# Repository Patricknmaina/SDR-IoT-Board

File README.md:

# SDR‑IoT‑Board

An IoT-based edge device and ground-station platform designed for telemetry and mission data—integrated with a 1U nanosatellite workflow. The hardware centers on an ESP32‑S3 module with LoRa, microSD storage, battery management/charging, sensor interfaces, and multiple expansion headers for rapid prototyping and deployment.

<p align="center">
  
  <br/>
  
  <br/>
  
  <br/>
</p>

## Table of Contents

- Overview
- Key Features
- Hardware Architecture
- Power Architecture
- Interfaces and Connectors
- Major Components
- Project Structure
- Manufacturing (Gerbers, BOM, CPL)
- Bring‑Up Checklist
- Firmware Getting Started
- Mechanical and 3D Models
- License
- Acknowledgements and Notes

## Overview

This repository contains the complete KiCad design for the IoT Edge Device v1.0, including schematic, PCB layout, fabrication outputs, custom footprints, and mechanical models. No firmware is included in this repository; the board is intended to be programmed using the ESP32‑S3’s native USB interface (ESP‑IDF or Arduino‑ESP32).

Use cases include ground-station telemetry collection, environmental sensing, edge data logging, and LoRa-based long-range links to remote nodes or satellite payload testbeds.

## Key Features

- ESP32‑S3‑WROOM‑1‑N16R8 module (16 MB flash, 8 MB PSRAM)
- LoRa radio module (Ai‑Thinker RA‑02, SPI interface)
- microSD storage (SPI mode selected; design notes on SPI vs. SDIO)
- Environmental sensing: BME280 (I2C; default address 0x76), DHT11 header
- Multiple I2C expansion headers for quick peripheral add‑ons
- Two UART headers for serial peripherals and diagnostics
- Relay driver header (external 5 V relay module), driven via ESP32‑S3 GPIO6 through 1 kΩ
- Native USB (Micro‑B) with ESD protection for data and power
- Battery management/boost via IP5306 module; status LEDs for charge/level
- 3.3 V rail via AMS1117‑3.3 LDO
- 32.768 kHz RTC crystal for ESP32‑S3 (ESR ≤ 70 kΩ per note)

## Hardware Architecture

- Microcontroller: ESP32‑S3‑WROOM‑1‑N16R8 (`IoT Edge Device v1.0/IoT Edge Device V1.kicad_sch`)
- Radio: RA‑02 LoRa (SPI: `MOSI_LORA`, `MISO_LORA`, `SCLK_LORA`, `CS_LORA`)
- Storage: microSD (SPI: `MOSI_SD`, `MISO_SD`, `SCLK_SD`, `CS_SD`)
- Sensors: BME280 on I2C (SDO pulled Low → default 0x76), DHT11 via single‑wire `DHT_DATA` header
- Expansion: three I2C headers (`SCL_OUT`, `SDA_OUT`), SPI header, UART1/2 headers
- Control: Relay header driven from ESP32‑S3 GPIO6 via 1 kΩ current‑limit resistor
- Clocking: 32.768 kHz crystal for RTC; ensure ESR ≤ 70 kΩ
- Protection: SP05xxx ESD array on USB; Schottky diodes for power ORing

Notes
- Design text documents the choice of SPI over SDIO for simplicity (SDIO is faster but higher complexity/CPU tradeoffs).
- Exact ESP32 GPIO mappings for the above nets are defined in the schematic; see the KiCad file for authoritative pinout and update firmware pin definitions accordingly.

## Power Architecture

- Sources: 5 V via USB Micro‑B and from IP5306 boost output; diode‑OR prevents back‑feeding.
- Solar input: 12 V panel → external LM7805 module → 5 V for IP5306 input (see design note). For higher efficiency and thermal margin, a buck regulator is recommended over linear.
- Battery: IP5306 manages charging and provides 5 V output; LED indicators for charge and capacity.
- 3.3 V rail: AMS1117‑3.3 LDO powers ESP32‑S3, LoRa, and sensors.

Recommendations
- Consider replacing the 12 V→5 V LM7805 path with a high‑efficiency buck (e.g., LM2596/MP1584) to reduce heat and increase battery/runtime performance.
- Validate 3.3 V load headroom (ESP32‑S3 + LoRa TX + SD activity) and thermal dissipation for the LDO.

## Interfaces and Connectors

- USB: Micro‑B connector; native ESP32‑S3 USB (D+ / D−) for flashing and CDC; ESD protection present.
- I2C: labeled I2C1 / I2C2 / I2C3 headers on `SCL_OUT` and `SDA_OUT` nets.
- SPI: dedicated header labeled “SPI Connector”.
- UART: UART1 and UART2 headers; UART2 noted for DAC use case.
- Relay: external 5 V relay module header; controlled by ESP32‑S3 GPIO6 via 1 kΩ series resistor.
- SD Card: microSD socket (SPI wiring).
- LoRa: RA‑02 module (SPI wiring with dedicated CS).

## Major Components

- X1: ESP32‑S3‑WROOM‑1‑N16R8 (MCU + Wi‑Fi/BLE, native USB)
- U6: Ai‑Thinker RA‑02 LoRa module (SPI)
- J15: microSD socket (Hirose DM3D‑SF)
- U8: BME280 environmental sensor (I2C, default 0x76)
- DHT11: external module via header (`DHT_DATA`)
- U5: IP5306 battery charger/boost controller
- U1: AMS1117‑3.3 linear regulator
- J1: USB Micro‑B connector
- D2: SP05xxx ESD protection for USB
- D4–D7: DFLS130L‑7 Schottky diodes (power ORing)
- Y1: 32.768 kHz crystal for RTC

See `IoT Edge Device v1.0/Fab Files/IoT BOM.csv` for the full sourced BOM (with JLCPCB part numbers) and `IoT Edge Device v1.0/Fab Files/IoT CPL.csv` for centroid/placements.

## Project Structure

- `IoT Edge Device v1.0/` — KiCad project (schematic, PCB, project metadata)
  - `IoT Edge Device V1.kicad_sch` — Schematic
  - `IoT Edge Device V1.kicad_pcb` — PCB layout
  - `Fab Files/` — Gerbers, drill, BOM, CPL for fabrication and assembly
  - `Fabrication Outputs.zip` — Consolidated fab package
- `Design Resources/` — Custom footprints and STEP models
- `Images/` — Renders and module screenshots used in this README

## Manufacturing (Gerbers, BOM, CPL)

All files required for fab and assembly are provided:

1) Gerbers and Drill
- Path: `IoT Edge Device v1.0/Fab Files/*gbr`, `.../IoT Edge Device V1.drl`

2) Bill of Materials
- Path: `IoT Edge Device v1.0/Fab Files/IoT BOM.csv` (includes JLCPCB part numbers)

3) Pick & Place (Centroid)
- Path: `IoT Edge Device v1.0/Fab Files/IoT CPL.csv` (Top placements)

## Firmware Getting Started

- Toolchains: ESP‑IDF (v5.x) or Arduino‑ESP32 with S3 support
- Transport: Native USB (CDC) for flashing and serial output
- Pin definitions: Map nets from the schematic to firmware pins:
  - LoRa SPI: `MOSI_LORA`, `MISO_LORA`, `SCLK_LORA`, `CS_LORA`
  - SD SPI: `MOSI_SD`, `MISO_SD`, `SCLK_SD`, `CS_SD`
  - I2C: `SDA_OUT`, `SCL_OUT`
  - DHT11: `DHT_DATA`
  - Relay: `GPIO6`

Since the ESP32 GPIO numbers tied to these nets can vary by routing, use the KiCad schematic (`.kicad_sch`) as the source of truth and set your firmware `gpio_num_t` values accordingly.

Libraries
- LoRa: `arduino-lmic` or `RadioLib` (Arduino), or ESP‑IDF SPI drivers with Semtech HAL equivalents
- microSD: `SD`/`SdFat` (Arduino) or ESP‑IDF `sdspi_host`
- BME280: Adafruit/ESP‑IDF drivers (I2C)
- DHT11: Adafruit (Arduino) or a simple single‑wire driver

## Mechanical and 3D Models

- STEP models for key parts are under `Design Resources/STEP Files/` (ESP32‑S3 module, RA‑02, IP5306, microSD, crystal, etc.)
- Use these for enclosure fit, heatsinking studies, and cable clearance.

## License

This project is released under the MIT License. See `LICENSE` for details.

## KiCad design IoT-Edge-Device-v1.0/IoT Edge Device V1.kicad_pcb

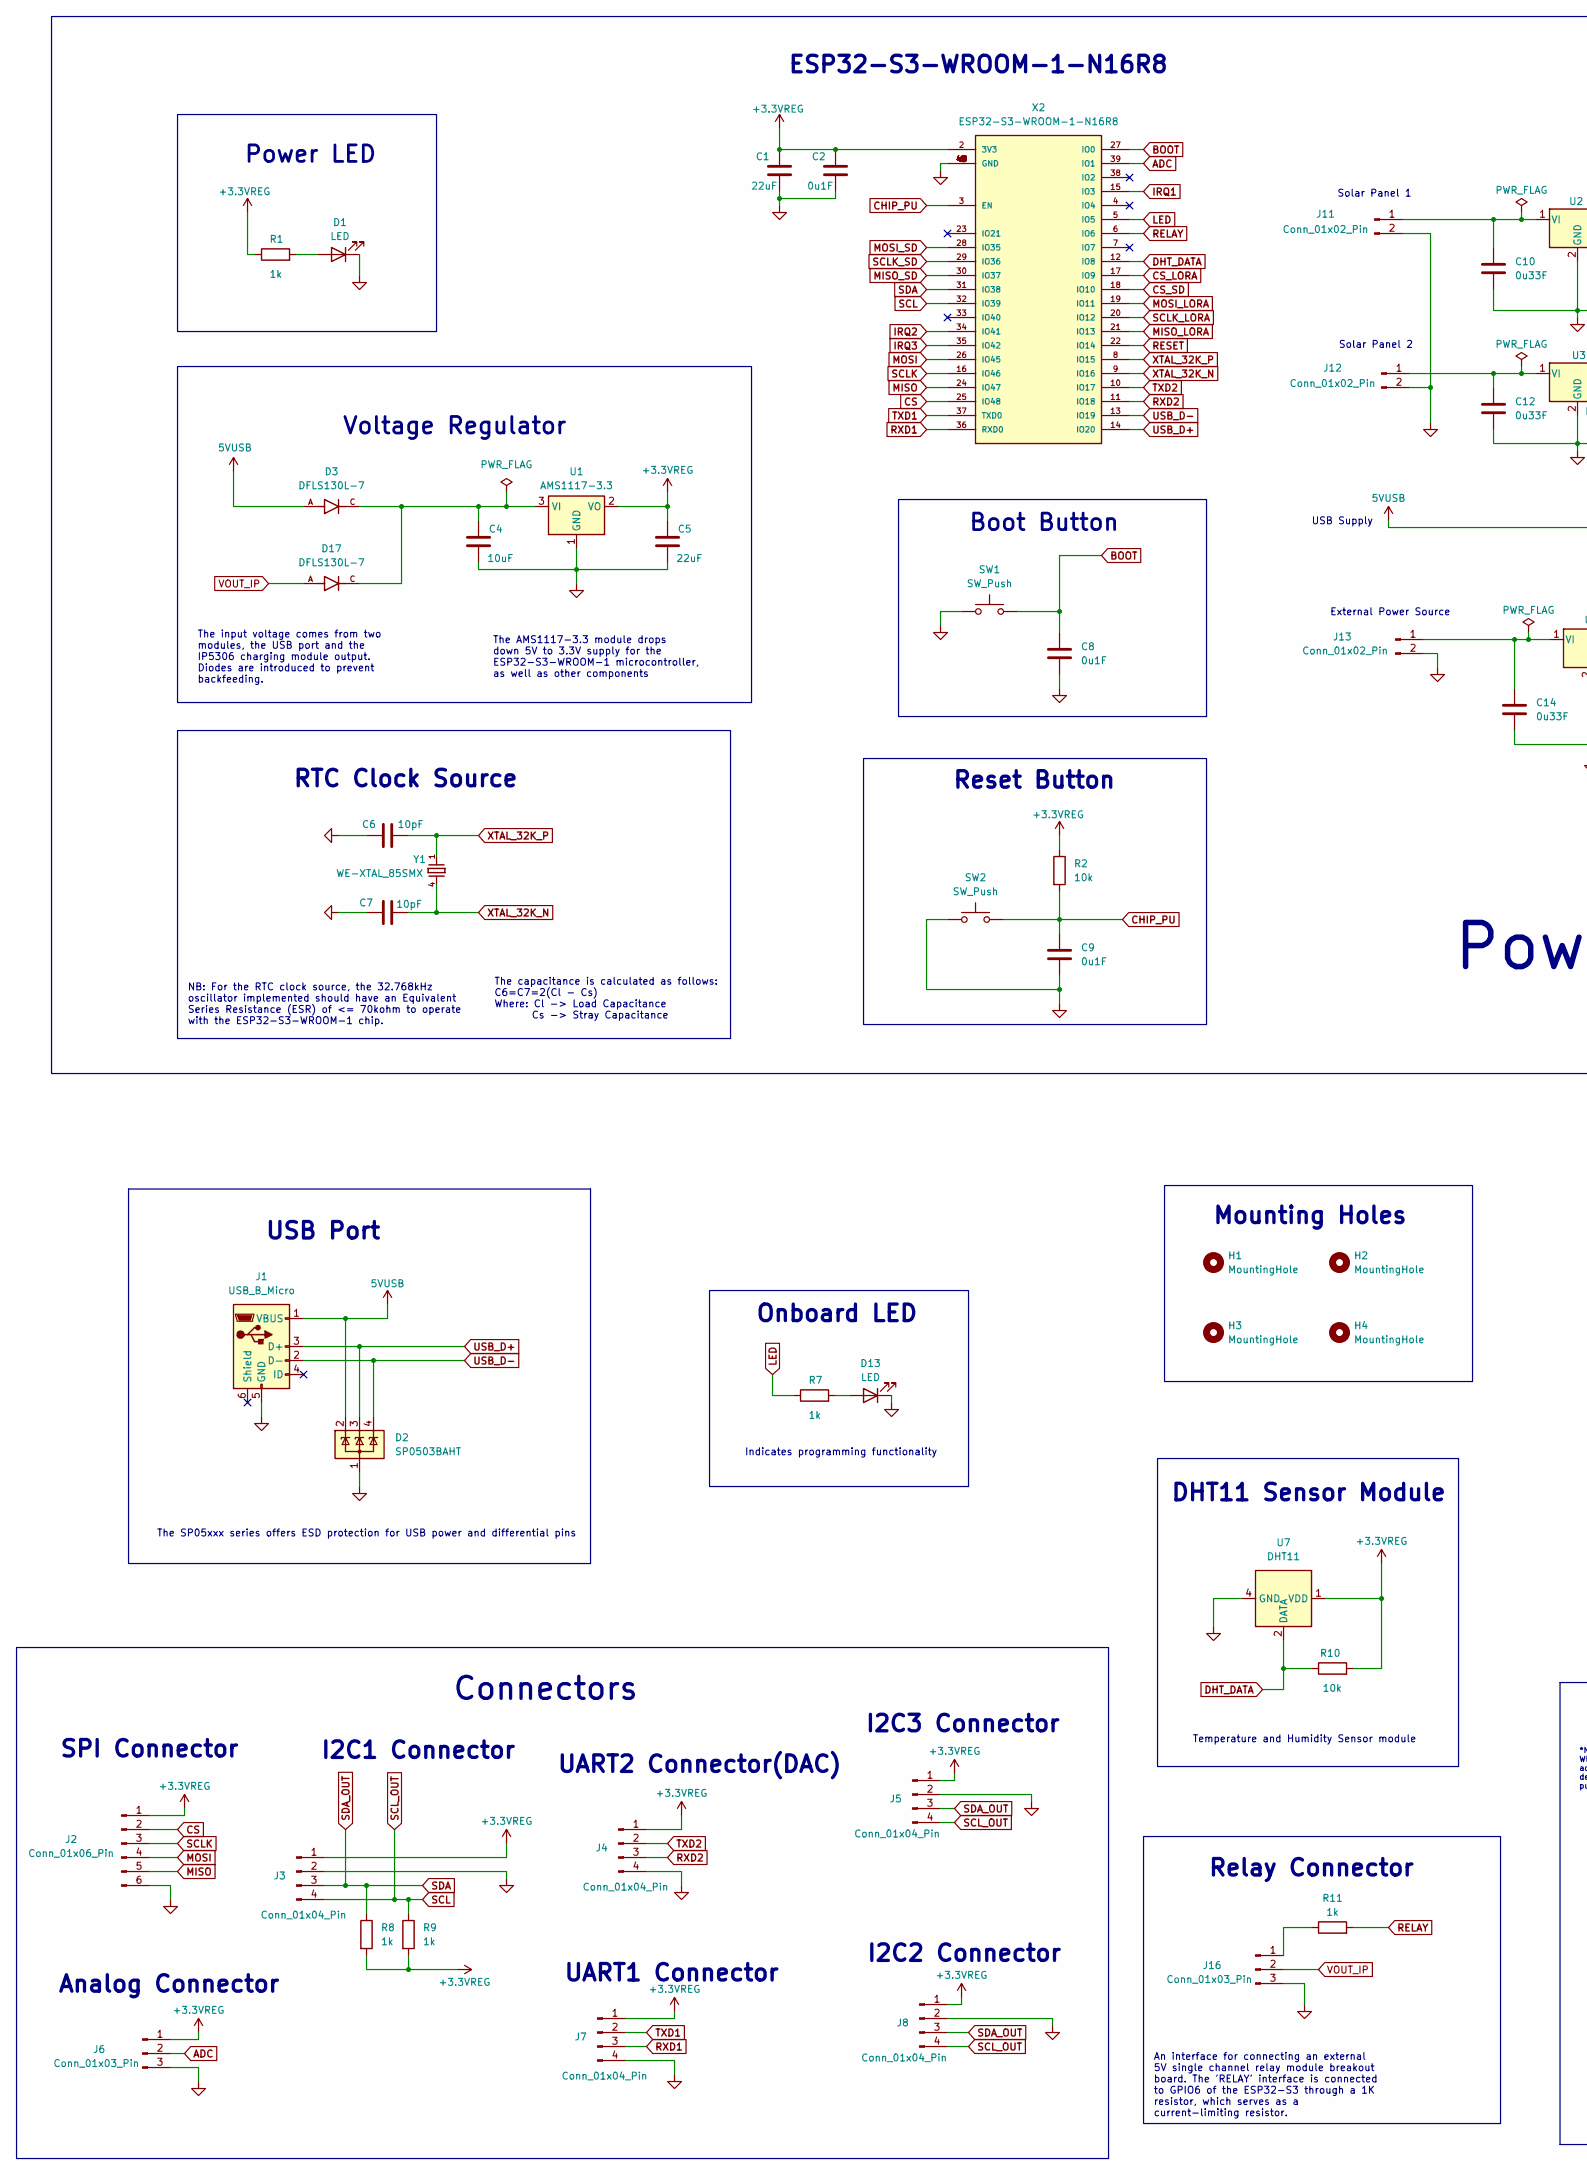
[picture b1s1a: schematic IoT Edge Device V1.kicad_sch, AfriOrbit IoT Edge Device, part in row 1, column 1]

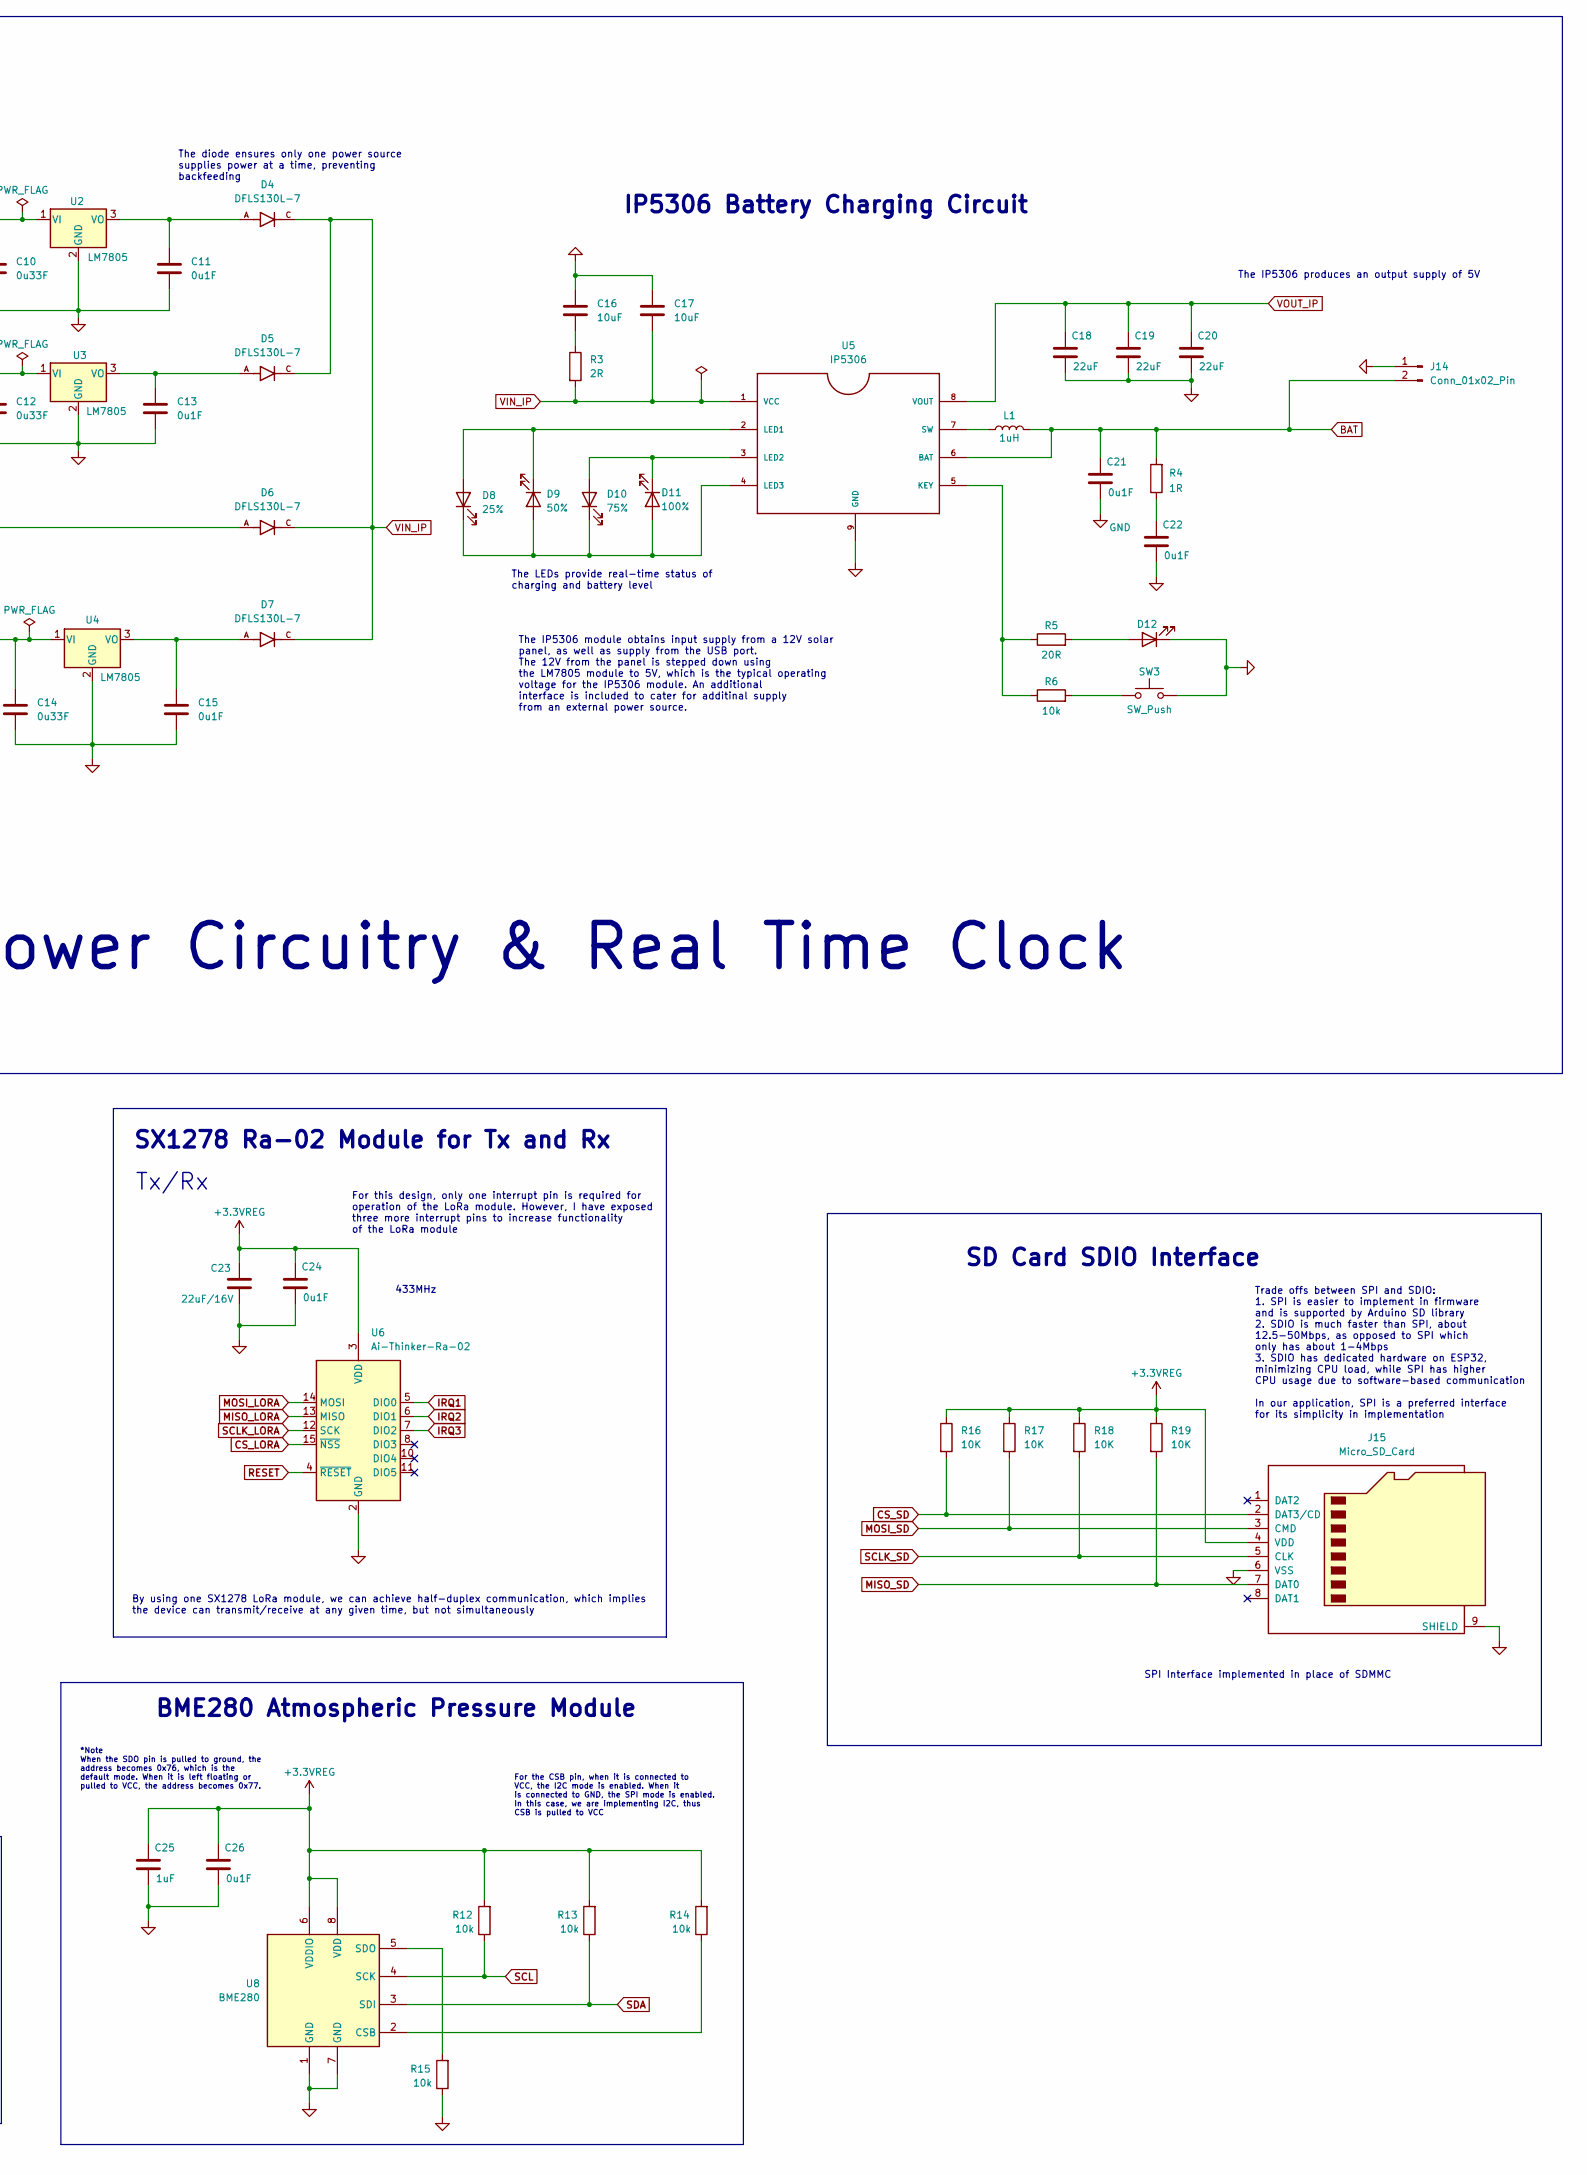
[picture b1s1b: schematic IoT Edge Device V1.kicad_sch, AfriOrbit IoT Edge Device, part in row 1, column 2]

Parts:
C1, C5, C18, C19, C20: 22uF; C_0603_1608Metric
C2, C8, C9, C11, C13, C15, C21, C22, C24, C26: 0u1F; C_0402_1005Metric
C4, C16, C17: 10uF; C_0402_1005Metric
C6, C7: 10pF; C_0402_1005Metric
C10, C12, C14: 0u33F; C_0402_1005Metric
C23: 22uF/16V; C_0603_1608Metric
C25: 1uF; C_0402_1005Metric
D1, D12, D13: LED; LED_0603_1608Metric
D2: SP0503BAHT; SOT-143
D3, D4, D5, D6, D7, D17: DFLS130L-7; DIO_DFLS130L-7; PARTREV 5 - 2
D8: 25%; LED_0603_1608Metric
D9: 50%; LED_0603_1608Metric
D10: 75%; LED_0603_1608Metric
D11: 100%; LED_0603_1608Metric
H1, H2, H3, H4: MountingHole; MountingHole_3.2mm_M3
J1: USB_B_Micro; USB_Micro-B_Wuerth_629105150521
J2: Conn_01x06_Pin; JST_XH_B6B-XH-A_1x06_P2.50mm_Vertical
J3, J4, J5, J7, J8: Conn_01x04_Pin; JST_XH_B4B-XH-A_1x04_P2.50mm_Vertical
J6, J16: Conn_01x03_Pin; JST_XH_B3B-XH-A_1x03_P2.50mm_Vertical
J11, J12, J13: Conn_01x02_Pin; JST_XH_B2B-XH-A_1x02_P2.50mm_Vertical
J14: Conn_01x02_Pin; PinHeader_1x02_P2.54mm_Vertical
J15: Micro_SD_Card; microSD_HC_Hirose_DM3D-SF
L1: 1uH; L_0402_1005Metric
R1, R7, R8, R9, R11: 1k; R_0402_1005Metric
R2, R6, R10, R12, R13, R14, R15: 10k; R_0402_1005Metric
R3: 2R; R_0402_1005Metric
R4: 1R; R_0402_1005Metric
R5: 20R; R_0402_1005Metric
R16, R17, R18, R19: 10K; R_0402_1005Metric
SW1, SW2, SW3: SW_Push; SW_PUSH_6mm
U1: AMS1117-3.3; SOT-223-3_TabPin2
U2, U3, U4: LM7805; TO-220-3_Vertical
U5: IP5306; SOIC9P127_490X600X170L84X42T330X241N
U6: Ai-Thinker-Ra-02; MODULE_RA-02_LORA
U7: DHT11; Aosong_DHT11_5.5x12.0_P2.54mm
U8: BME280; Bosch_LGA-8_2.5x2.5mm_P0.65mm_ClockwisePinNumbering
X2: ESP32-S3-WROOM-1-N16R8; ESP32S3WROOM1N8R2; MANUFACTURER_PART_NUMBER ESP32-S3-WROOM-1-N16R8
Y1: WE-XTAL_85SMX

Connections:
5VUSB: D2.2 (K), D3.A, D6.A, J1.1 (VBUS)
+3.3VREG: C1.1, C2.1, C5.1, C23.1, C24.1, C25.1, C26.1, J2.1, J3.1, J4.1, J5.1, J6.1, J7.1, J8.1, J15.4 (VDD), R1.1, R2.1, R8.2, R9.2, R10.2, R12.2, R13.2, R14.2, R16.1, R17.1, R18.1, R19.1, U1.2 (VO), U6.3 (VDD), U7.1 (VDD), U8.6 (VDDIO), U8.8 (VDD), X2.2 (3V3); also elsewhere on the board
ADC: J6.2, X2.39 (IO1); also elsewhere on the board
BAT: C21.1, J14.2, L1.2, R4.2, U5.6 (BAT)
BOOT: C8.1, SW1.2, X2.27 (IO0); also elsewhere on the board
CHIP_PU: C9.1, R2.2, SW2.2, X2.3 (EN); also elsewhere on the board
CS: J2.2, X2.25 (IO48); also elsewhere on the board
CS_LORA: U6.15 (~NSS), X2.17 (IO9); also elsewhere on the board
CS_SD: J15.2 (DAT3/CD), R16.2, X2.18 (IO10); also elsewhere on the board
DHT_DATA: R10.1, U7.2 (DATA), X2.12 (IO8); also elsewhere on the board
GND: C1.2, C2.2, C4.2, C5.2, C6.1, C7.1, C8.2, C9.2, C10.2, C11.2, C12.2, C13.2, C14.2, C15.2, C16.1, C17.1, C18.2, C19.2, C20.2, C21.2, C22.2, C23.2, C24.2, C25.2, C26.2, D1.1 (K), D2.1 (A), D12.1 (K), D13.1 (K), J1.5 (GND), J2.6, J3.2, J4.4, J5.2, J6.3, J7.4, J8.2, J11.2, J12.2, J13.2, J14.1, J15.6 (VSS), J15.9 (SHIELD), J16.3, R15.1, SW1.1, SW2.1, SW3.2, U1.1 (GND), U2.2 (GND), U3.2 (GND), U4.2 (GND), U5.9 (GND), U6.1 (GND), U6.2 (GND), U6.9 (GND), U6.16 (GND), U7.4 (GND), U8.1 (GND), U8.7 (GND), X2.1 (GND), X2.40 (GND), X2.41 (GND), X2.42 (GND), X2.43 (GND), X2.44 (GND), X2.45 (GND), X2.46 (GND), X2.47 (GND), X2.48 (GND), X2.49 (GND); also elsewhere on the board
IRQ1: U6.5 (DIO0), X2.15 (IO3); also elsewhere on the board
IRQ2: U6.6 (DIO1), X2.34 (IO41); also elsewhere on the board
IRQ3: U6.7 (DIO2), X2.35 (IO42); also elsewhere on the board
LED: R7.1, X2.5 (IO5); also elsewhere on the board
MISO: J2.5, X2.24 (IO47); also elsewhere on the board
MISO_LORA: U6.13 (MISO), X2.21 (IO13); also elsewhere on the board
MISO_SD: J15.7 (DAT0), R19.2, X2.30 (IO37); also elsewhere on the board
MOSI: J2.4, X2.26 (IO45); also elsewhere on the board
MOSI_LORA: U6.14 (MOSI), X2.19 (IO11); also elsewhere on the board
MOSI_SD: J15.3 (CMD), R17.2, X2.28 (IO35); also elsewhere on the board
unnamed: C16.2, R3.1
unnamed: C22.1, R4.1
unnamed: D1.2 (A), R1.2
unnamed: D8.2 (A), D9.1 (K), U5.2 (LED1)
unnamed: D10.2 (A), D11.1 (K), U5.3 (LED2)
unnamed: D8.1 (K), D9.2 (A), D10.1 (K), D11.2 (A), U5.4 (LED3)
unnamed: D12.2 (A), R5.2
unnamed: D13.2 (A), R7.2
unnamed: C10.1, J11.1, U2.1 (VI)
unnamed: C12.1, J12.1, U3.1 (VI)
unnamed: C14.1, J13.1, U4.1 (VI)
unnamed: J16.1, R11.1
unnamed: R6.2, SW3.1
unnamed: C4.1, D3.C, D17.C, U1.3 (VI)
unnamed: C11.1, D4.A, U2.3 (VO)
unnamed: C13.1, D5.A, U3.3 (VO)
unnamed: C15.1, D7.A, U4.3 (VO)
unnamed: R5.1, R6.1, U5.5 (KEY)
unnamed: L1.1, U5.7 (SW)
unnamed: R14.1, U8.2 (CSB)
unnamed: R15.2, U8.5 (SDO)
RELAY: R11.2, X2.6 (IO6); also elsewhere on the board
RESET: U6.4 (~RESET), X2.22 (IO14); also elsewhere on the board
RXD1: J7.3, X2.36 (RXD0); also elsewhere on the board
RXD2: J4.3, X2.11 (IO18); also elsewhere on the board
SCL: J3.4, J5.4, J8.4, R9.1, R12.1, U8.4 (SCK), X2.32 (IO39); also elsewhere on the board
SCLK: J2.3, X2.16 (IO46); also elsewhere on the board
SCLK_LORA: U6.12 (SCK), X2.20 (IO12); also elsewhere on the board
SCLK_SD: J15.5 (CLK), R18.2, X2.29 (IO36); also elsewhere on the board
SDA: J3.3, J5.3, J8.3, R8.1, R13.1, U8.3 (SDI), X2.31 (IO38); also elsewhere on the board
TXD1: J7.2, X2.37 (TXD0); also elsewhere on the board
TXD2: J4.2, X2.10 (IO17); also elsewhere on the board
USB_D+: D2.3 (K), J1.3 (D+), X2.14 (IO20); also elsewhere on the board
USB_D-: D2.4 (K), J1.2 (D-), X2.13 (IO19); also elsewhere on the board
VIN_IP: C17.2, D4.C, D5.C, D6.C, D7.C, R3.2, U5.1 (VCC)
VOUT_IP: C18.1, C19.1, C20.1, D17.A, J16.2, U5.8 (VOUT)
XTAL_32K_N: C7.2, X2.9 (IO16), Y1.4; also elsewhere on the board
XTAL_32K_P: C6.2, X2.8 (IO15), Y1.1; also elsewhere on the board

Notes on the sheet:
SPI Connector
The capacitance is calculated as follows: C6=C7=2(Cl - Cs) Where: Cl -> Load Capacitance Cs -> Stray Capacitance
The input voltage comes from two modules, the USB port and the IP5306 charging module output. Diodes are introduced to prevent backfeeding.
I2C1 Connector
The IP5306 produces an output supply of 5V
*Note When the SDO pin is pulled to ground, the address becomes 0x76, which is the default mode. When it is left floating or pulled to VCC, the address becomes 0x77.
Mounting Holes
USB Port
UART2 Connector(DAC)
Tx/Rx
433MHz
BME280 Atmospheric Pressure Module
SX1278 Ra-02 Module for Tx and Rx
Connectors
Temperature and Humidity Sensor module
By using one SX1278 LoRa module, we can achieve half-duplex communication, which implies the device can transmit/receive at any given time, but not simultaneously
An interface for connecting an external 5V single channel relay module breakout board. The 'RELAY' interface is connected to GPIO6 of the ESP32-S3 through a 1K resistor, which serves as a current-limiting resistor.
Analog Connector
Power Circuitry & Real Time Clock
I2C3 Connector
Relay Connector
NB: For the RTC clock source, the 32.768kHz oscillator implemented should have an Equivalent Series Resistance (ESR) of <= 70kohm to operate with the ESP32-S3-WROOM-1 chip.
RTC Clock Source
I2C2 Connector
For the CSB pin, when it is connected to VCC, the I2C mode is enabled. When it is connected to GND, the SPI mode is enabled. In this case, we are implementing I2C, thus CSB is pulled to VCC
Boot Button
UART1 Connector
SPI Interface implemented in place of SDMMC
The IP5306 module obtains input supply from a 12V solar panel, as well as supply from the USB port. The 12V from the panel is stepped down using the LM7805 module to 5V, which is the typical operating voltage for the IP5306 module. An additional interface is included to cater for additinal supply f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
The LEDs provide real-time status of charging and battery level
Voltage Regulator
Trade offs between SPI and SDIO: 1. SPI is easier to implement in firmware and is supported by Arduino SD library 2. SDIO is much faster than SPI, about 12.5-50Mbps, as opposed to SPI which only has about 1-4Mbps 3. SDIO has dedicated hardware on ESP32, minimizing CPU load, while SPI has higher CPU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
Onboard LED
Reset Button
ESP32-S3-WROOM-1-N16R8
Power LED
Indicates programming functionality
DHT11 Sensor Module
Solar Panel 1
IP5306 Battery Charging Circuit

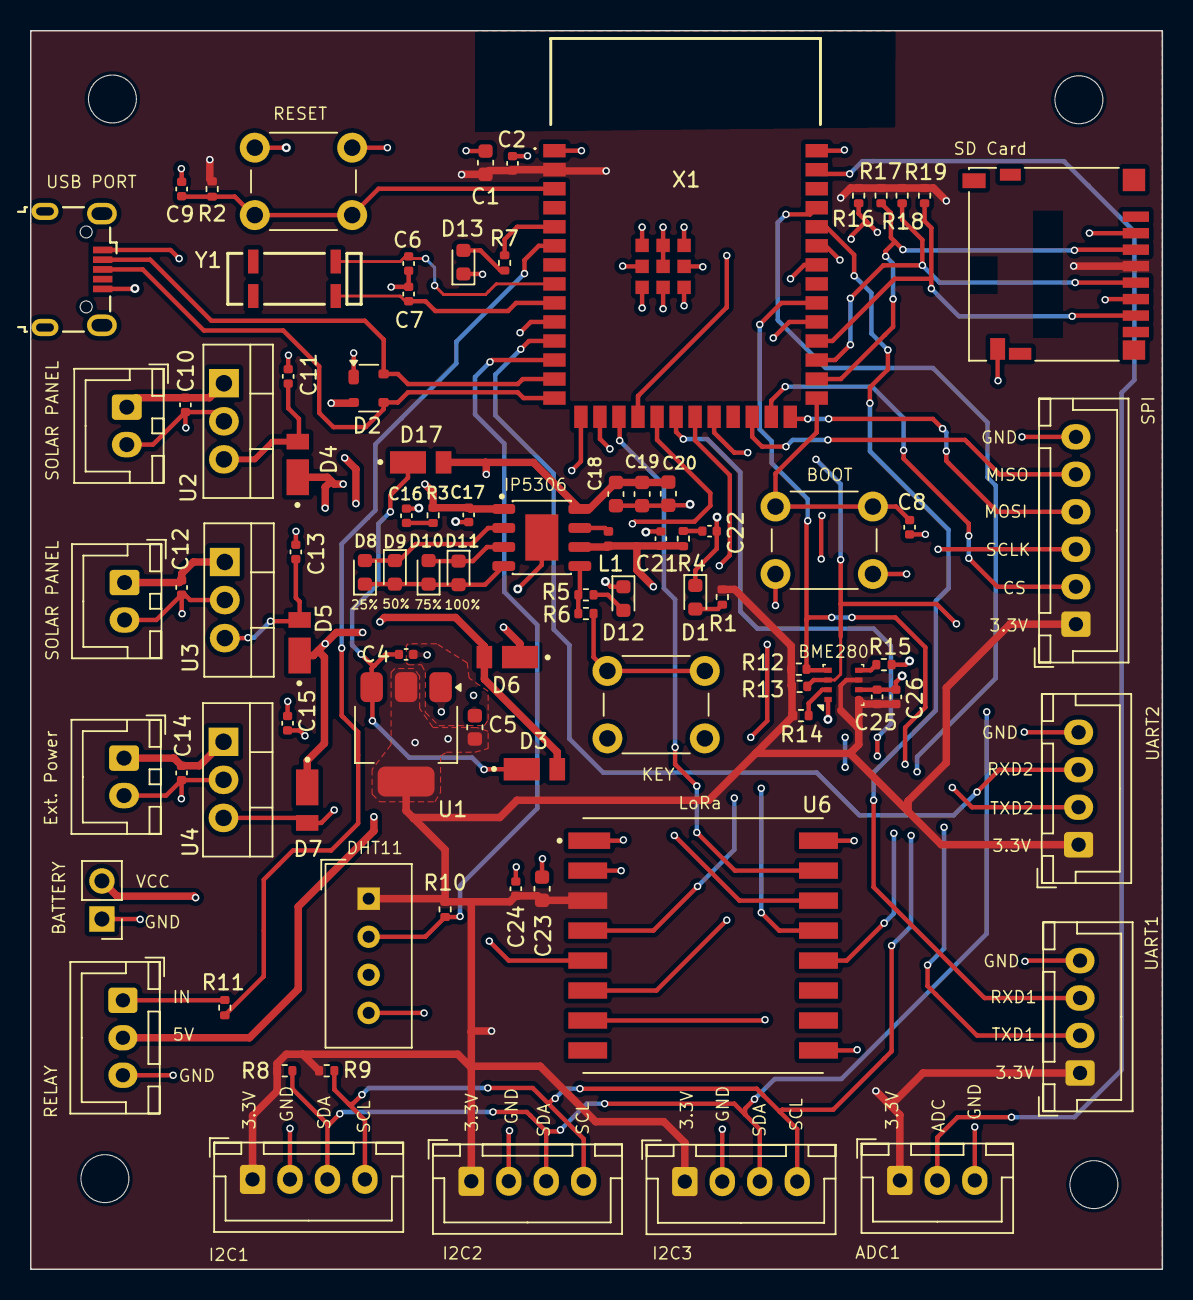
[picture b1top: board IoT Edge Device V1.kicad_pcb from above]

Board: 4 copper layers, 75.5 x 82.7 mm, 90 parts (0 on the bottom side), 59 nets.

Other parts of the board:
X1: ESP32-S3-WROOM-1-N16R8; ESP32S3WROOM1N8R2

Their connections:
+3.3VREG: X1.2 (3V3); also elsewhere on the board
ADC: X1.39 (IO1); also elsewhere on the board
BOOT: X1.27 (IO0); also elsewhere on the board
CHIP_PU: X1.3 (EN); also elsewhere on the board
CS: X1.25 (IO48); also elsewhere on the board
CS_LORA: X1.17 (IO9); also elsewhere on the board
CS_SD: X1.18 (IO10); also elsewhere on the board
DHT_DATA: X1.12 (IO8); also elsewhere on the board
GND: X1.1 (GND), X1.40 (GND), X1.41 (GND), X1.42 (GND), X1.43 (GND), X1.44 (GND), X1.45 (GND), X1.46 (GND), X1.47 (GND), X1.48 (GND), X1.49 (GND); also elsewhere on the board
IRQ1: X1.15 (IO3); also elsewhere on the board
IRQ2: X1.34 (IO41); also elsewhere on the board
IRQ3: X1.35 (IO42); also elsewhere on the board
LED: X1.5 (IO5); also elsewhere on the board
MISO: X1.24 (IO47); also elsewhere on the board
MISO_LORA: X1.21 (IO13); also elsewhere on the board
MISO_SD: X1.30 (IO37); also elsewhere on the board
MOSI: X1.26 (IO45); also elsewhere on the board
MOSI_LORA: X1.19 (IO11); also elsewhere on the board
MOSI_SD: X1.28 (IO35); also elsewhere on the board
RELAY: X1.6 (IO6); also elsewhere on the board
RESET: X1.22 (IO14); also elsewhere on the board
RXD1: X1.36 (RXD0); also elsewhere on the board
RXD2: X1.11 (IO18); also elsewhere on the board
SCL: X1.32 (IO39); also elsewhere on the board
SCLK: X1.16 (IO46); also elsewhere on the board
SCLK_LORA: X1.20 (IO12); also elsewhere on the board
SCLK_SD: X1.29 (IO36); also elsewhere on the board
SDA: X1.31 (IO38); also elsewhere on the board
TXD1: X1.37 (TXD0); also elsewhere on the board
TXD2: X1.10 (IO17); also elsewhere on the board
USB_D+: X1.14 (IO20); also elsewhere on the board
USB_D-: X1.13 (IO19); also elsewhere on the board
XTAL_32K_N: X1.9 (IO16); also elsewhere on the board
XTAL_32K_P: X1.8 (IO15); also elsewhere on the board

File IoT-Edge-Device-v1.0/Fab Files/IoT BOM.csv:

Comment,Designator,Footprint,JLCPCB Part #
22uF Unpolarized capacitor,"C1,C5,C18,C19,C20",Capacitor_SMD:C_0603_1608Metric,C59461
0.1uF Unpolarized capacitor,"C2,C8,C9,C11,C13,C15,C21,C22,C24,C26",Capacitor_SMD:C_0402_1005Metric,C14663
1uF Unpolarized capacitor,"C3,C25",Capacitor_SMD:C_0402_1005Metric,C15849
10uF Unpolarized capacitor,"C4,C16,C17",Capacitor_SMD:C_0402_1005Metric,C19702
10pF Unpolarized capacitor,"C6,C7",Capacitor_SMD:C_0402_1005Metric,C1634
0.33uF Unpolarized capacitor,"C10,C12,C14",Capacitor_SMD:C_0402_1005Metric,C3039642
22uF/16V Unpolarized capacitor,C23,Capacitor_SMD:C_0603_1608Metric,C5116073
Red Power Light emitting diode (LED),D1,LED_SMD:LED_0603_1608Metric,C965799
Blue IP5306 Key Status LED,D12,LED_SMD:LED_0603_1608Metric,C965807
Green Status LED,D13,LED_SMD:LED_0603_1608Metric,C22371297
"SP0503BAHT TVS Diode Array, 5.5V Standoff, 3 Channels, SOT-143 package",D2,Package_TO_SOT_SMD:SOT-143,C7074
DFLS130L-7,"D4,D5,D6,D7",DFLS130L-7:DIO_DFLS130L-7,C110493
"25%, 50%, 75% Light emitting diode (Red)","D8, D9, D10",LED_SMD:LED_0603_1608Metric,C965799
100% Light emitting diode (Green),D11,LED_SMD:LED_0603_1608Metric,C22371297
"1000V 1A General Purpose Rectifier Diode, DO-41",D14,Diode_SMD:D_0603_1608Metric,C727081
Relay Green Status LED,D15,LED_SMD:LED_0603_1608Metric,C22371297
Relay Red Power LED,D16,LED_SMD:LED_0603_1608Metric,C965799
USB Micro Type B connector,J1,Connector_USB:USB_Micro-B_Wuerth_629105150521,C2894326
Micro SD Card Socket,J15,Connector_Card:microSD_HC_Hirose_DM3D-SF,C719027
1uH Inductor,L1,Inductor_SMD:L_0402_1005Metric,C531288
1k Resistor,"R1,R4,R5,R15,R16,R17,R18",Resistor_SMD:R_0402_1005Metric,C11702
10k Resistor,"R2,R3,R9,R10,R11,R12,R13,R14,R19,R20,R21,R22",Resistor_SMD:R_0402_1005Metric,C25744
2R Resistor,R6,Resistor_SMD:R_0402_1005Metric,C2906922
1R Resistor,R7,Resistor_SMD:R_0402_1005Metric,C137904
20R Resistor,R8,Resistor_SMD:R_0402_1005Metric,C310214
"1A Low Dropout regulator, positive, 3.3V fixed output, SOT-223 (AMS1117-3.3)",U1,Package_TO_SOT_SMD:SOT-223-3_TabPin2,C347222
"Ai-Thinker Ra-02 410-525 MHz LoRa Module, SPI interface, U.FL antenna connector",U6,RA-02_LORA:MODULE_RA-02_LORA,C90039
"3-in-1 sensor, humidity, pressure, temperature, I2C and SPI interface, 1.71-3.6V, LGA-8 (BME280)",U8,Package_LGA:Bosch_LGA-8_2.5x2.5mm_P0.65mm_ClockwisePinNumbering,C92489
IP5306,U5,IP5306:SOIC9P127_490X600X170L84X42T330X241N,C181692
ESP32-S3-WROOM-1-N16R8 Module,X1,ESP32-S3-WROOM-1-N16R8:ESP32S3WROOM1N8R2,C2913202
WE-XTAL-85SMX Crystal Oscillator,Y1,WE-XTAL_85SMX:WE-XTAL_85SMX,N/A

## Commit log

2025-10-27 added design files and documentation
2025-10-29 updated the project README
